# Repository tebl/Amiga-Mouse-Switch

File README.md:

# Amiga Mouse Switch
The first port on the Amiga is usually dedicated to a mouse, which is why a lot of the cracker-intros added to games seem to require you to click the mouse button to actually load the game. Unfortunately, this means that in order to load a two-player game you'd have to unplug the mouse and then plug in the joystick again so that player 2 has any chance of controlling anything. Restarting the computer or starting a new game means you'll have to do the *two-cable merengue* all over again.

The easy solution is to simply buy one of the many adapters that allows you to switch between the mouse and a joystick at the push of a button, but as I like building things I've attempted to make a new version of it - in part by just copying parts of the [C64 Joystick Switcher](https://github.com/tebl/C64-Joystick-Switcher) that in many ways is very similar. I also took some inspiration from reading the December 1991 article in Elektor Magazine, unfortunately locked behind a paywall.

- [1> Building the unit](#1-building-the-unit)
  - [1.1> Soldering it together](#11-soldering-it-together)
  - [1.2> Assembling the unit](#12-assembling-the-unit)
  - [1.3> Cable bits](#13-cable-bits)
  - [1.4> Testing it out](#14-testing-it-out)
  - [1.5> Errata](#15-errata)
- [2> Schematic](#2-schematic)
- [3> BOM](#3-bom)

# 1> Building the unit
Building the unit assumes you have at least minor experience soldering things together, recommended is at least a soldering station with adjustable temperature to get started - usually you'll want some 60/40 solder tin (if you can get that where you live). With the equipment sorted, now comes the shopping. So head on over to the [BOM](#3-bom)-section for some information on what you need, with eBay, AliExpress and similar sites you'll need to treat these as a starting search term and get what seems to match up to the gallery pictures.

The following are pictures of a bare board, the second is one that I have assembled the way I prefer them. The *AUTO*-jumpers have been linked meaning that the board will automatically make the switch for you, this is done when either the primary fire button on your joystick have been pressed - or - you've pressed the left button on your mouse. Without the two linked you'd need to install the two switches, and then use those to switch between the two. The latter mode may be preferred as this leaves the right mouse button as a second fire button while you're using the joystick (that way an accidental left-click won't swap over to your mouse). If that sounds weird to you then go for the *AUTO*-mode.

## 1.1> Soldering it together
The construction of this unit should be straight-forward, beginning with the single diode found on the board. This needs to be installed in the correct orientation, basically by matching up the black stripe with the corresponding markings on the PCB-silkscreen (that's the white markings if it's your first attempt at soldering something together).

Then do the resistors, and as for the ones marked with the values *330* you'll need to pick something that's suitable for the LEDs that you're going to use (if any). The incredibly cheap LEDs with dyed plastic can use the value as indicated, but for anything that seems *clear*, *cloudy* or *blue* - then you're going to need something else. 1k, 2k2 or even 3k3 may be a more suitable value for you. If you're unsure, leave them for last and try to poke one of each into the holes - then solder in the one that you prefer.

Moving on, I've linked the *AUTO*-jumpers as described earlier. They might be a bit annoying to do on your first attempts, but just try to heat both pads at once and keep feeding in solder until a blob forms between the two. If it still won't stick right, just keep moving between them and you'll get there before long.

DIP-sockets goes in next. You *might* be able to skip installing these for a cheaper construction, but I wouldn't do so unless I explicitly *know* that my chips came from reliable sources (they almost never do). It has an indent on one side, and it should be matched up with the half-circle on the silkscreen. They work the same when installed the other way around, but it's only a question of time before that little trick sees you putting a chip in the wrong way.

There are some yellow capacitors added, these have a 5mm pin spacing and as for the type I just use these yellow monolithic type of capacitors instead of the older ceramic discs based on looks alone. There might be some difference between the two, but none that are relevant at this point so use what you have - as long as it has been marked with the value *104* (100nF, also equivalent to 0.1uF depending on how the vendor choose to list them).

Next, solder in the IDC socket, the gap should point inwards and will match the illustration on the board itself. LEDs goes in next, these are used to indicate the currently active device - the shorter pin goes into the hole surrounded by a **square** pad. In order to ensure that the faceplate will fit properly, you should only barely tack one of the pins into place - then reheat and push it completely flush against the board.

The male right-angle DB9 connectors should be straight-forward to install, just slot them into place and solder until satisfied that it won't be going anywhere. Be careful when soldering in the anchor points as it's easy to burn yourself when trying to hold it into place, so do the pins first if you're unsure about this step.

At this point you'll already have seen the need to decide if you want the mouse switcher to, well - switch automatically between the joystick and mouse - or - if it should remain a manual switcher. If you want to use the switches in combination with a faceplate, you'll need to use the B-variant of faceplates as those have a cutout in it for the switches. As for the switches, you'll need to find some that are sufficiently long enough so that they can poke through the PCB. The switches I'm using were sourced from eBay and AliExpress, listed as *6x6x9mm momentary tactile switches* - if in doubt, get a kit with various lengths and pick the one that you prefer. 

## 1.2> Assembling the unit
Insert ICs into the sockets as indicated, ensuring that the indent matches the orientation on the board - plugging them in the wrong way ensures that you'll have to order some more. Double-check before even considering plugging it into something, use the picture below as reference.

The standard A1 faceplate can be reversed to match the look you want the unit to have, at some point in the far flung future I'll hopefully have some 1bit artwork suitable to put on it. If you bought the *M3 nylon hex kit* as suggested, you can use four of the 8mm standoffs on each corner of the main PCB - fix them on the bottom using M3 nuts (snip off the remaining part of the nylon screw). Place the faceplate on top, screw it into place using - well - M3 nylon screws. Use wire cutters to cut off any metal parts protruding further down than the M3 nuts, this is just so that nothing messes up your desk surface.

If you have an extra PCB, consider putting it on the bottom so that nothing accidentally shorts out on any kind of metal that you'd have laying around on your desk during gameplay. That's just a pro-tip for people with access to more than they need, alternatively you could just cover it all with a any kind of plastic sheet that can easily be cut into the correct shape.

## 1.3> Cable bits
I've gone into extensive detail on making up the joystick cables, so for a more detailed explanation skip on over to the [C64 JoyKEY](https://github.com/tebl/C64-JoyKEY/blob/main/documentation/building.md#building-the-cables) documentation to see how I did it there. Essentially you just take a *2x5 pin IDC JTAG AVR cable* (common ebay listing description), find the end that fits nicely into the keying on the board and cut off the other. Take a female IDC flat cable DB9 connector, match up pin 1 with the red stripe on the cable and squeeze really hard with something to lock it into place on the cable. Wrap the cable over and push the strain relief on the connector.

## 1.4> Testing it out
There isn't many viable options for testing things out without actually plugging it into something and seeing whether the thing actually works as intended. One alternative to testing on a vintage computer is using a joystick tester, but given that those don't exactly follow a defined standard - the only one I can suggest is the [Atari Joystick Tester](https://github.com/tebl/Atari-Joystick-Tester) - if it's one of those that run on a coin-cell battery, then it definitely won't work. Pushing the joystick fire button or the left mouse button will switch the active port, as long as you enabled the auto-function - if not you'll have to use the switches on the device itself.

When testing on the Amiga, either as the first or second step,  I suggest using something like [Amiga Test Kit](https://github.com/keirf/Amiga-Stuff/releases) - ensuring that the device as well as the machine itself works as intended.

## 1.5> Errata
Some users have reported problems using the right mouse button with the current design, so I had a little think about it and simplified it a bit for revision C. Essentially the option to have a second joystick button that isn't generally used, for earlier revision B the changes would be to remove and short across the space marked with "D4", then cut the line going to pin 9 on the joystick port. In order to add scroll-wheel support, a link was added that links mouse pin 5 to output pin 5.

# 2> Schematic
The supplied KiCad files should be sufficient as both a schematic and as a  starting point for ordering PCBs (basically you could just zip the contents of the export folder and upload that on a fabrication site), the schematic is also available in [PDF-format](documentation/schematic) and this is what you'll need to print and work your way through this things don't work as expected after assembly.

# 3> BOM
Most parts should be easy to get a hold of from your favourite local electronic component shop, but given that I don't have access to such shops where I live so everything was based on whatever I could get cheapest from eBay/AliExpress (free shipping, but plan on waiting 3-4 weeks for delivery). Values listed in parenthesis are for features that are not required for basic functionality, but you should read through the section on [building the unit](#1-building-the-unit) to ensure that you're not missing out. As always, plan on adding DIP-sockets in addition to the chips listed.

| Reference        | Item                                                           | Count | Order  |
| ---------------- | -------------------------------------------------------------- | ----- | ------ |
| PCB              | Fabricate using Gerber files                                   |     1 | [PCBWay](https://www.pcbway.com/project/shareproject/Amiga_Mouse_Switch.html)
| PCB Faceplate A1 | Fabricate using Gerber files                                   |    (1)| [PCBWay](https://www.pcbway.com/project/shareproject/Amiga_Mouse_Switch__Faceplate_A1_.html)
| PCB Faceplate B1 | Fabricate using Gerber files                                   |    (1)| PCBWay |
| C1-C3            | 100nF ceramic capacitor (5mm)                                  |     3 |
| D1,D2            | 5mm LED                                                        |    (2)|
| D3               | 1n4148 diode DO-35                                             |     1 | 
| J1,J2            | Female DB9 right-angle connector                               |     2 |
| J3 *             | 2x5 pin male IDC socket                                        |     1 |
| R1,R2            | 10k Ohm resistor                                               |     2 |
| R3,R4            | 330 Ohm resistor                                               |    (2)|
| SW1,SW2          | 6x6x9mm momentary button                                       |    (2)|
| U1,U2            | 74HCT4053 or CD4053 (DIP-16)                                   |     2 |
| U3               | NE555 (DIP-8)                                                  |     1 |
| DB9 cable **     | Ribbon cable (9 wires), DB-9 female IDC and 2x5 pin female IDC |     1 |
| Mounting ***     | M3x8mm nylon HEX standoff                                      |    (4)|
| Mounting ***     | M3x6mm nylon hex screw                                         |    (4)|
| Mounting ***     | M3 nylon nut                                                   |    (4)|

*) Can use regular double row pin headers, but it is recommended to use IDC socket as it has keying.

**) You can buy the ribbon cable, DB9 female IDC connector and 2x5 pin female IDC. The easiest however is just buying something that already has the female DB9 connector attached to a ribbon cable, then just cut off the DB9 end - finally, add the 2x5 pin female IDC connector. Pictures on my [C64 JoyKEY](https://github.com/tebl/C64-JoyKEY/blob/main/documentation/building.md#building-the-cables)-repository as that uses the exact same cable.

***) The easiest way of ordering these is to just one of the M3 nylon standoff kits on ebay, AliExpress or any similar sites. That way you'll get more than what you need in various sizes for future projects as well.

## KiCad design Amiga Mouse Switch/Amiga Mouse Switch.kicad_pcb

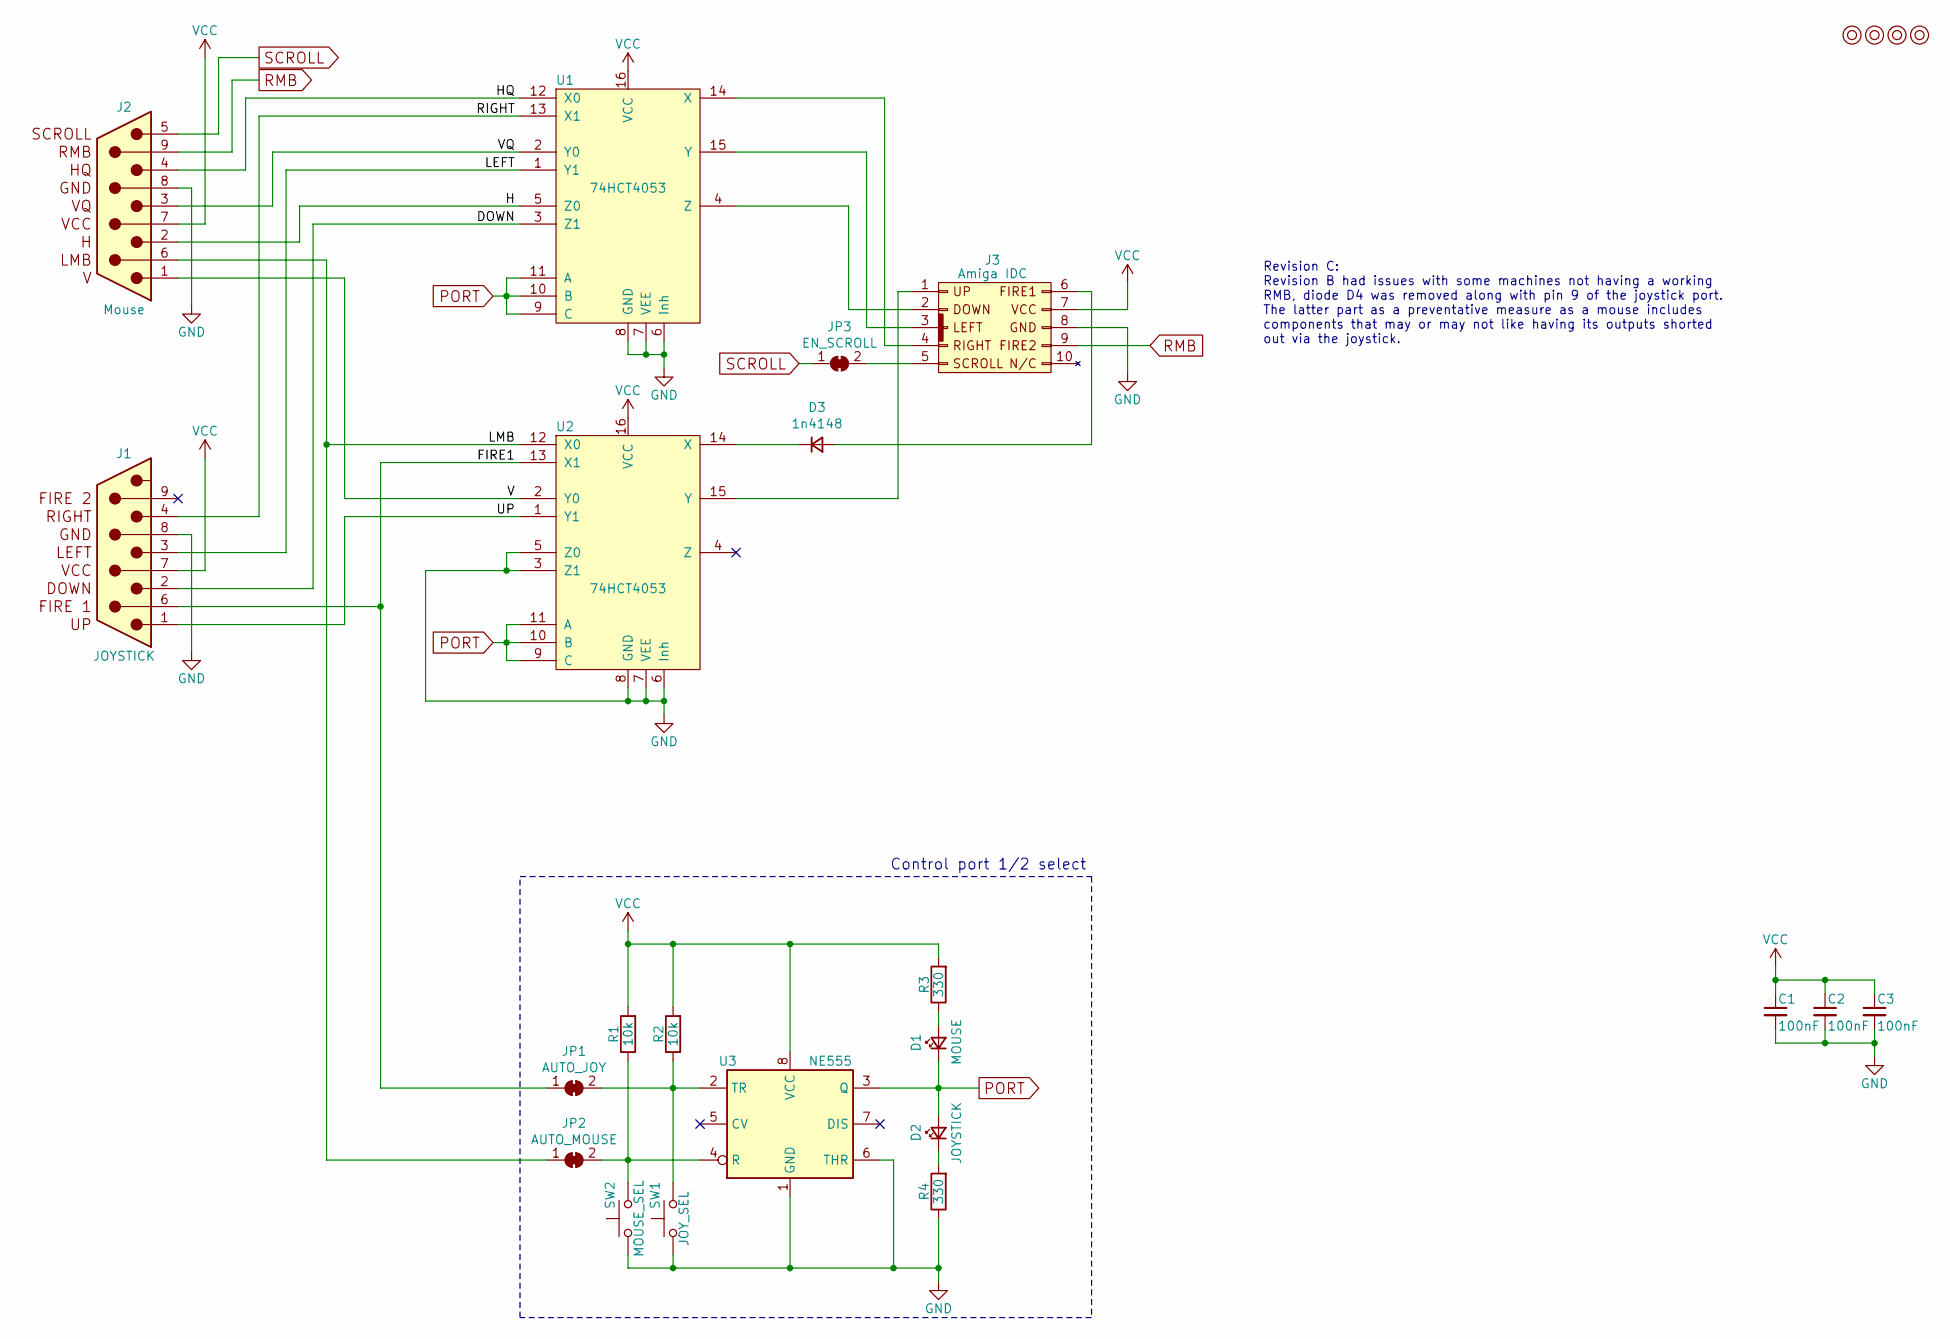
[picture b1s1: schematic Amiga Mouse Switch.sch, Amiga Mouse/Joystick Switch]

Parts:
C1, C2, C3: 100nF; C_Disc_D4.7mm_W2.5mm_P5.00mm
D1: MOUSE; LED_D5.0mm
D2: JOYSTICK; LED_D5.0mm
D3: 1n4148; D_DO-35_SOD27_P7.62mm_Horizontal
J1: JOYSTICK; DSUB-9_Male_Horizontal_P2.77x2.84mm_EdgePinOffset7.70mm_Hou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
J2: Mouse; DSUB-9_Male_Horizontal_P2.77x2.84mm_EdgePinOffset7.70mm_Hou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
J3: Amiga IDC; IDC_Joystick
JP1: AUTO_JOY; bridge
JP2: AUTO_MOUSE; bridge
JP3: EN_SCROLL; bridge
M1, M2, M3, M4: Mounting; M3_pin
R1, R2: 10k; R_Axial_DIN0207_L6.3mm_D2.5mm_P10.16mm_Horizontal
R3, R4: 330; R_Axial_DIN0207_L6.3mm_D2.5mm_P10.16mm_Horizontal
SW1: JOY_SEL; SW_PUSH_6mm
SW2: MOUSE_SEL; SW_PUSH_6mm
U1, U2: 74HCT4053; DIP-16_W7.62mm_Socket_LongPads
U3: NE555; DIP-8_W7.62mm_Socket_LongPads

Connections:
/DOWN: J1.2, U1.3 (Z1)
/FIRE1: J1.6, JP1.1 (A), U2.13 (X1)
/H: J2.2, U1.5 (Z0)
/HQ: J2.4, U1.12 (X0)
/LEFT: J1.3, U1.1 (Y1)
/LMB: J2.6, JP2.1 (A), U2.12 (X0)
/RIGHT: J1.4, U1.13 (X1)
/UP: J1.1, U2.1 (Y1)
/V: J2.1, U2.2 (Y0)
/VQ: J2.3, U1.2 (Y0)
GND: C1.2, C2.2, C3.2, J1.8 (GND), J2.8 (GND), J3.8, R4.1, SW1.1, SW2.1, U1.6 (Inh), U1.7 (VEE), U1.8 (GND), U2.3 (Z1), U2.5 (Z0), U2.6 (Inh), U2.7 (VEE), U2.8 (GND), U3.1 (GND), U3.6 (THR)
unnamed: D1.2 (A), R3.1
unnamed: D2.1 (K), R4.2
unnamed: D3.1 (K), U2.14 (X)
unnamed: D3.2 (A), J3.6
unnamed: J3.1, U2.15 (Y)
unnamed: J3.2, U1.4 (Z)
unnamed: J3.3, U1.15 (Y)
unnamed: J3.4, U1.14 (X)
unnamed: J3.5, JP3.2 (B)
unnamed: JP1.2 (B), R2.1, SW1.2, U3.2 (TR)
unnamed: JP2.2 (B), R1.1, SW2.2, U3.4 (R)
PORT: D1.1 (K), D2.2 (A), U1.9 (C), U1.10 (B), U1.11 (A), U2.9 (C), U2.10 (B), U2.11 (A), U3.3 (Q)
RMB: J2.9, J3.9
SCROLL: J2.5 (SCROLL), JP3.1 (A)
VCC: C1.1, C2.1, C3.1, J1.7 (VCC), J2.7 (VCC), J3.7, R1.2, R2.2, R3.2, U1.16 (VCC), U2.16 (VCC), U3.8 (VCC)

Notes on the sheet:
Control port 1/2 select
Revision C: Revision B had issues with some machines not having a working RMB, diode D4 was removed along with pin 9 of the joystick port. The latter part as a preventative measure as a mouse includes components that may or may not like having its outputs shorted out via the joystick.

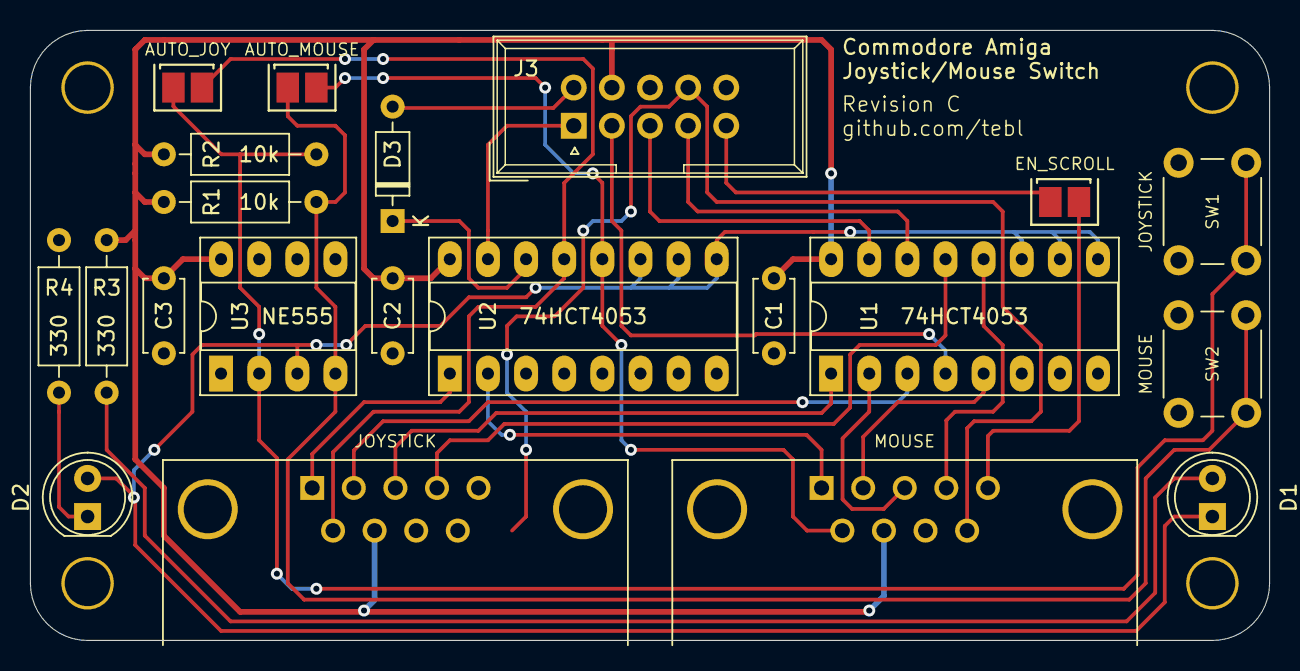
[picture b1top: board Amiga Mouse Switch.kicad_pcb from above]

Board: 2 copper layers, 82.5 x 40.6 mm, 25 parts (0 on the bottom side), 26 nets.

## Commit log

2021-02-12 Started project
2021-02-12 Schematic done
2021-02-12 Add libraries
2021-02-13 Layout done
2021-02-13 Gerber export
2021-02-13 Visual tweaks
2021-02-14 Basic faceplate layout
2021-03-09 Added diode for lines that have pull-ups onboard
2021-03-14 Added images
2021-03-14 Fixed RMB
2021-03-14 Added B1 faceplate
2021-03-14 Added README
2021-03-14 Reordered build images (need revision B update later)
2021-03-14 Changed wording
2021-03-14 Added image
2023-11-17 Old build images
2023-11-17 Tweaks for RMB (untested)
2025-01-05 New build images
2025-01-05 Updated documentation
2025-01-05 Missing link
